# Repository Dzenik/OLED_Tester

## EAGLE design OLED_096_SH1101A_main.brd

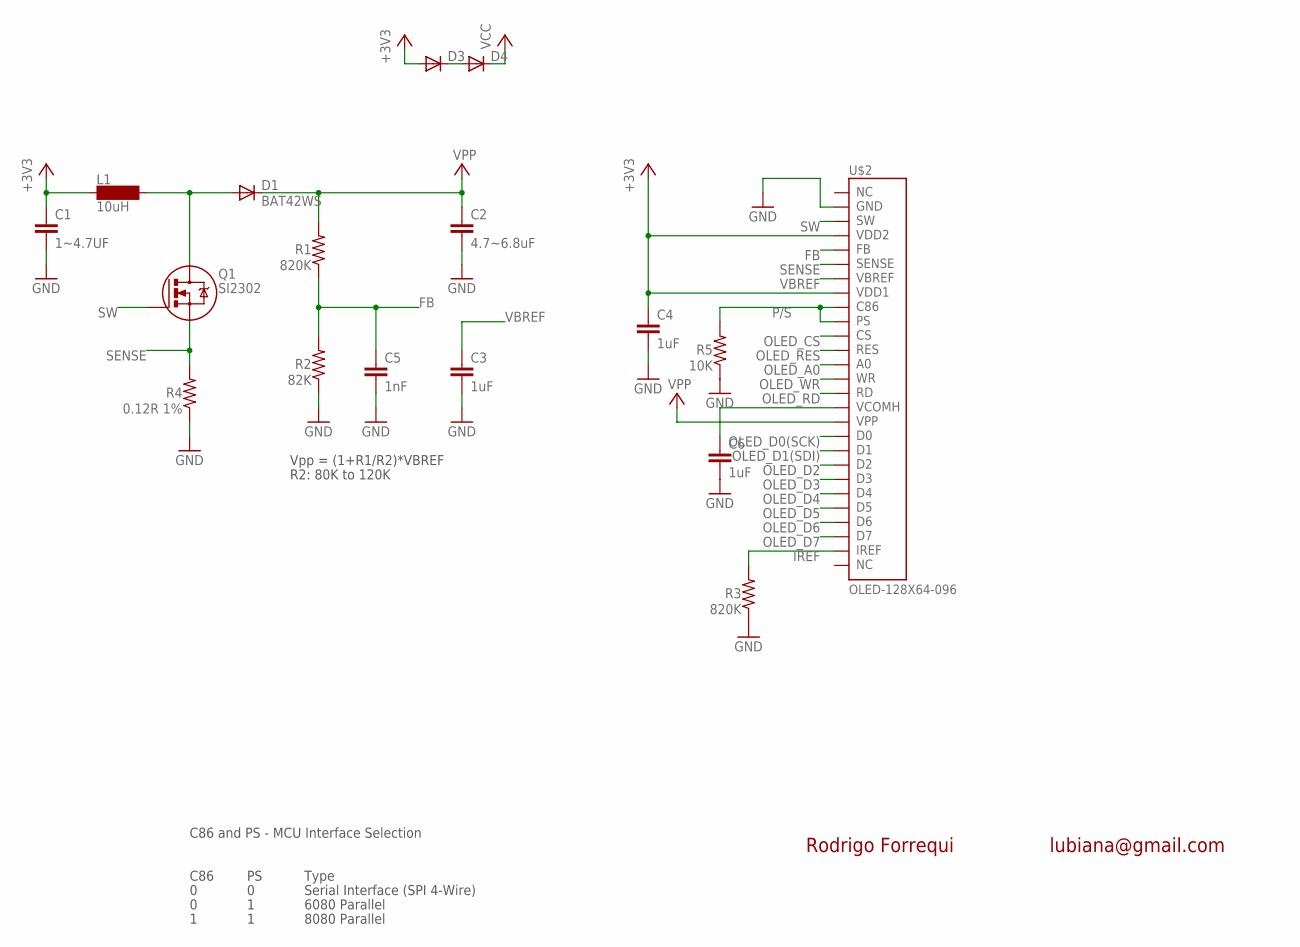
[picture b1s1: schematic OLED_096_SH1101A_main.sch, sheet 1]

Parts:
C1: 1~4.7UF; C0805
C2: 4.7~6.8uF; C0805
C3, C4, C6: 1uF; C0805
C5: 1nF; C0805
D1: BAT42WS; SOD-323
D3, D4: DIODE-MINIMELF; MINIMELF
L1: 10uH; LPO4812
Q1: SI2302; SOT23-3
R1, R3: 820K; R0805
R2: 82K; R0805
R4: 0.12R 1%; M1206
R5: 10K; R0805
U$2: OLED-128X64-096; UG-2864AMBAG01

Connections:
+3V3: C1.1, C4.1, D3.A, L1.P$1 (1), U$2.P$4, U$2.P$8
FB: C5.1, R1.1, R2.2, U$2.P$5
GND: C1.2, C2.2, C3.2, C4.2, C5.2, C6.2, R2.1, R3.1, R4.1, R5.1, U$2.P$2; also elsewhere on the board
IREF: R3.2, U$2.P$26
unnamed: D1.2 (A), L1.P$2 (2), Q1.3 (D)
unnamed: C6.1, U$2.P$16
unnamed: D3.C, D4.A
OLED_A0: U$2.P$13; also elsewhere on the board
OLED_CS: U$2.P$11; also elsewhere on the board
OLED_D0(SCK): U$2.P$18; also elsewhere on the board
OLED_D1(SDI): U$2.P$19; also elsewhere on the board
OLED_D2: U$2.P$20
OLED_D3: U$2.P$21
OLED_D4: U$2.P$22
OLED_D5: U$2.P$23
OLED_D6: U$2.P$24
OLED_D7: U$2.P$25
OLED_RD: U$2.P$15
OLED_RES: U$2.P$12; also elsewhere on the board
OLED_WR: U$2.P$14
P/S: R5.2, U$2.P$9, U$2.P$10
SENSE: Q1.2 (S), R4.2, U$2.P$6
SW: Q1.1 (G), U$2.P$3
VBREF: C3.1, U$2.P$7
VCC: C2.1, D1.1 (C), D4.C, R1.2, U$2.P$17; also elsewhere on the board

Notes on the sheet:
C86 and PS - MCU Interface Selection
C86
Type
8080 Parallel
6080 Parallel
Serial Interface (SPI 4-Wire)
Vpp = (1+R1/R2)*VBREF
R2: 80K to 120K
Rodrigo Forrequi
lubiana@gmail.com

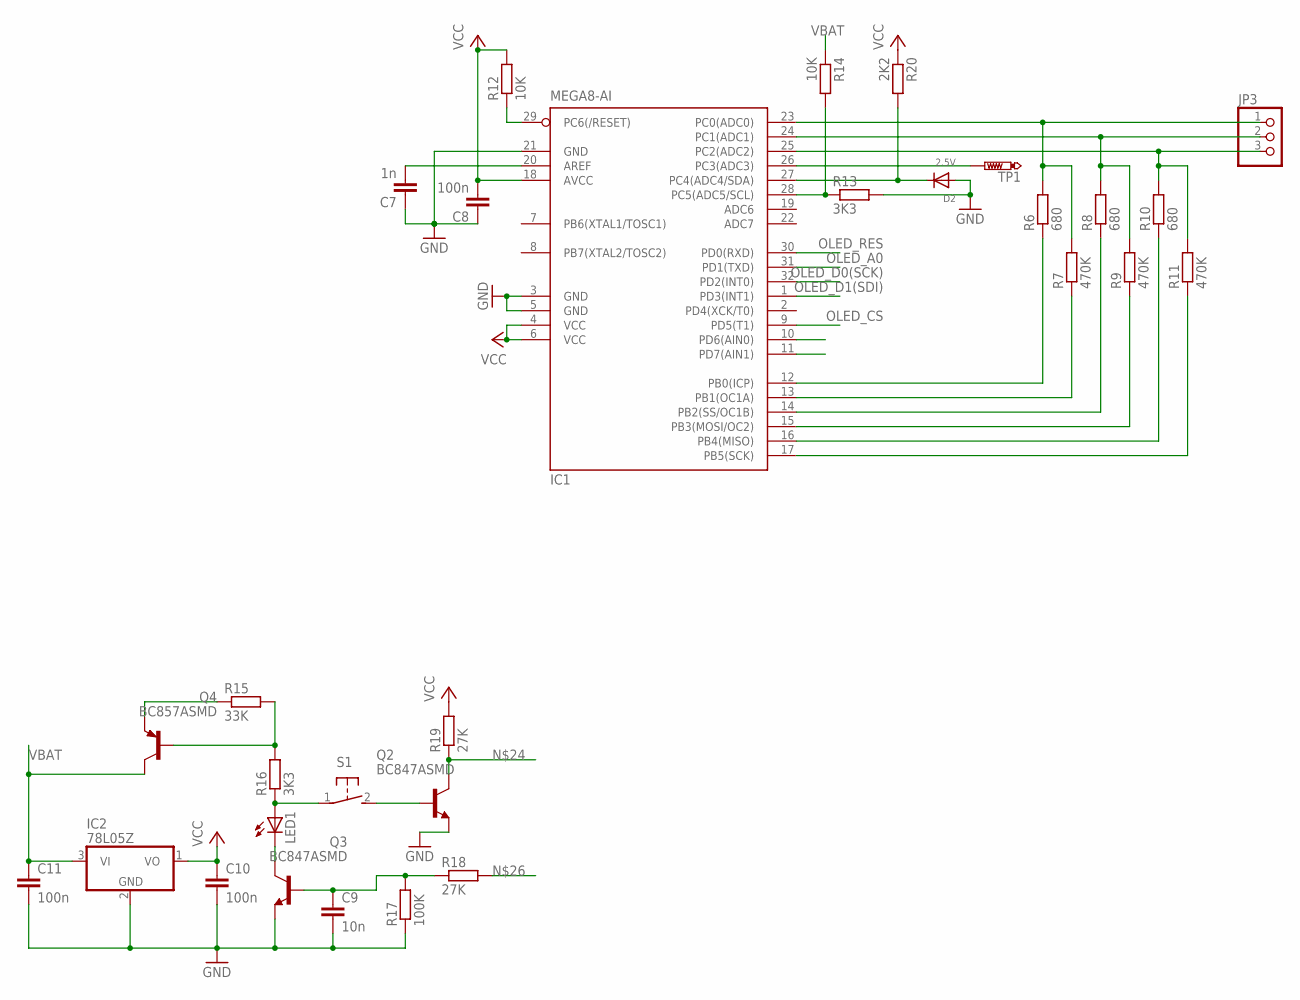
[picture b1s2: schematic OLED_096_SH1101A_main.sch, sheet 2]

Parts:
C7: 1n; C0805
C8, C10, C11: 100n; C0805
C9: 10n; C0805
D2: 2.5V; SOD-523
IC1: MEGA8-AI; TQFP32-08
IC2: 78L05Z; TO92
JP3: PINHD-1X3; 1X03
LED1: LEDSML0603; SML0603
Q2, Q3: BC847ASMD; SOT23
Q4: BC857ASMD; SOT23-BEC
R6, R8, R10: 680; R0805
R7, R9, R11: 470K; R0805
R12, R14: 10K; R0805
R13, R16: 3K3; R0805
R15: 33K; R0805
R17: 100K; R0805
R18, R19: 27K; R0805
R20: 2K2; R0805
S1: 31-XX; B3F-31XX
TP1: PTR1B1,27; B1,27

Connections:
GND: C7.1, C8.1, C9.2, C10.2, C11.2, D2.A, IC1.3 (GND), IC1.5 (GND), IC1.21 (GND), IC2.2 (GND), Q2.2 (E), Q3.2 (E), R13.2, R17.1; also elsewhere on the board
unnamed: IC1.23 (PC0(ADC0)), JP3.1, R6.2, R7.2
unnamed: IC1.24 (PC1(ADC1)), JP3.2, R8.2, R9.2
unnamed: IC1.25 (PC2(ADC2)), JP3.3, R10.2, R11.2
unnamed: IC1.12 (PB0(ICP)), R6.1
unnamed: IC1.13 (PB1(OC1A)), R7.1
unnamed: IC1.14 (PB2(SS/OC1B)), R8.1
unnamed: IC1.15 (PB3(MOSI/OC2)), R9.1
unnamed: IC1.16 (PB4(MISO)), R10.1
unnamed: IC1.17 (PB5(SCK)), R11.1
unnamed: C7.2, IC1.20 (AREF)
unnamed: IC1.28 (PC5(ADC5/SCL)), R13.1, R14.2
unnamed: IC1.29 (PC6(/RESET)), R12.1
unnamed: D2.K (C), IC1.27 (PC4(ADC4/SDA)), R20.2
unnamed: IC1.26 (PC3(ADC3)), TP1.TP
unnamed: C9.1, Q3.1 (B), R17.2, R18.1
unnamed: LED1.A, R16.1, S1.1
unnamed: LED1.C, Q3.3 (C)
unnamed: Q2.1 (B), S1.2 (S)
unnamed: Q4.B, R15.2, R16.2
unnamed: Q4.E, R15.1
unnamed: IC1.11 (PD7(AIN1)), Q2.3 (C), R19.1
unnamed: IC1.10 (PD6(AIN0)), R18.2
OLED_A0: IC1.31 (PD1(TXD)); also elsewhere on the board
OLED_CS: IC1.9 (PD5(T1)); also elsewhere on the board
OLED_D0(SCK): IC1.32 (PD2(INT0)); also elsewhere on the board
OLED_D1(SDI): IC1.1 (PD3(INT1)); also elsewhere on the board
OLED_RES: IC1.30 (PD0(RXD)); also elsewhere on the board
VBAT: C11.1, IC2.3 (VI), Q4.C, R14.1
VCC: C8.2, C10.1, IC1.4 (VCC), IC1.6 (VCC), IC1.18 (AVCC), IC2.1 (VO), R12.2, R19.2, R20.1; also elsewhere on the board

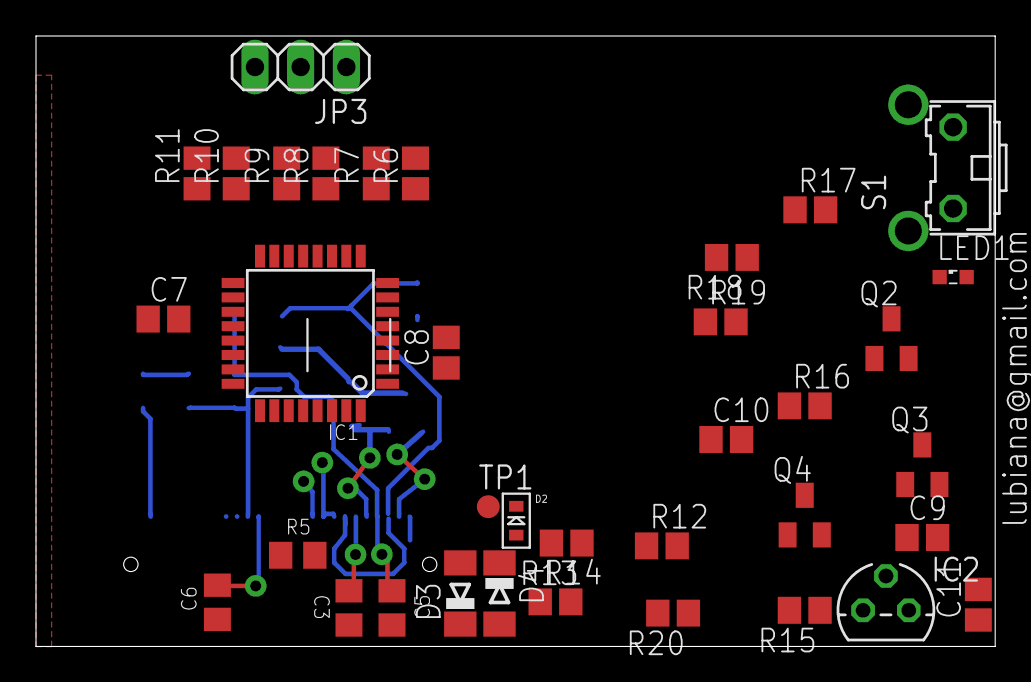
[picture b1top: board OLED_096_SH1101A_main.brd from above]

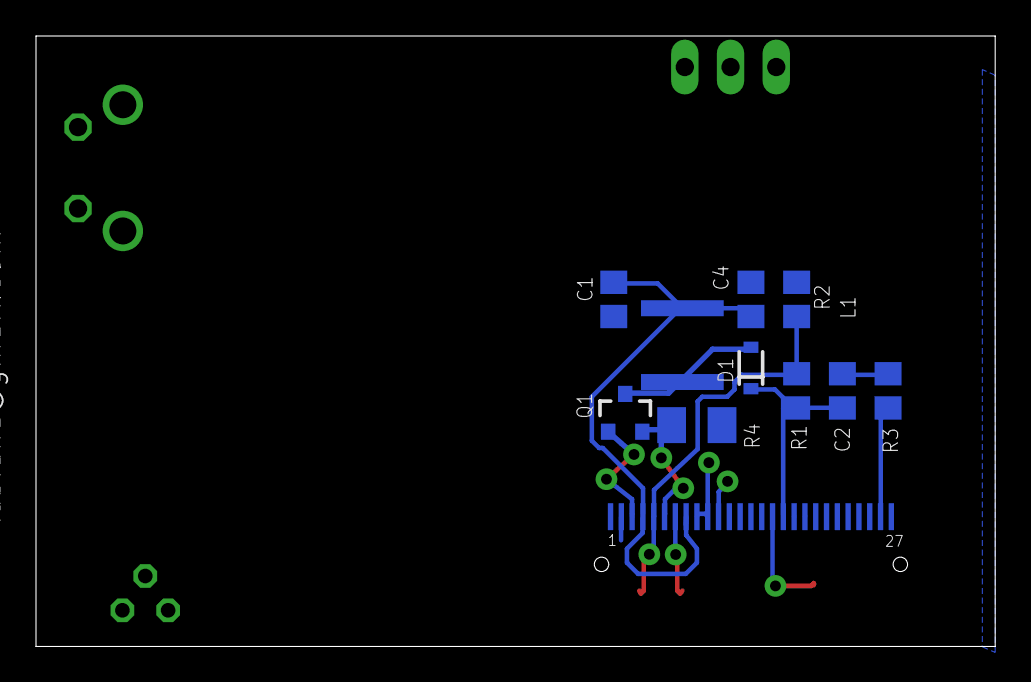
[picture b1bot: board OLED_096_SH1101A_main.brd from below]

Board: 2 copper layers, 53.3 x 33.9 mm, 47 parts (11 on the bottom side), 40 nets.

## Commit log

2015-07-02 Initial not working!
2015-07-03 Fix schematic
